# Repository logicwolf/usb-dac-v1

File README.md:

# usb-dac-v1

This is project for making the usb-dac with pcm2707 and es9023 - 2017.01.24

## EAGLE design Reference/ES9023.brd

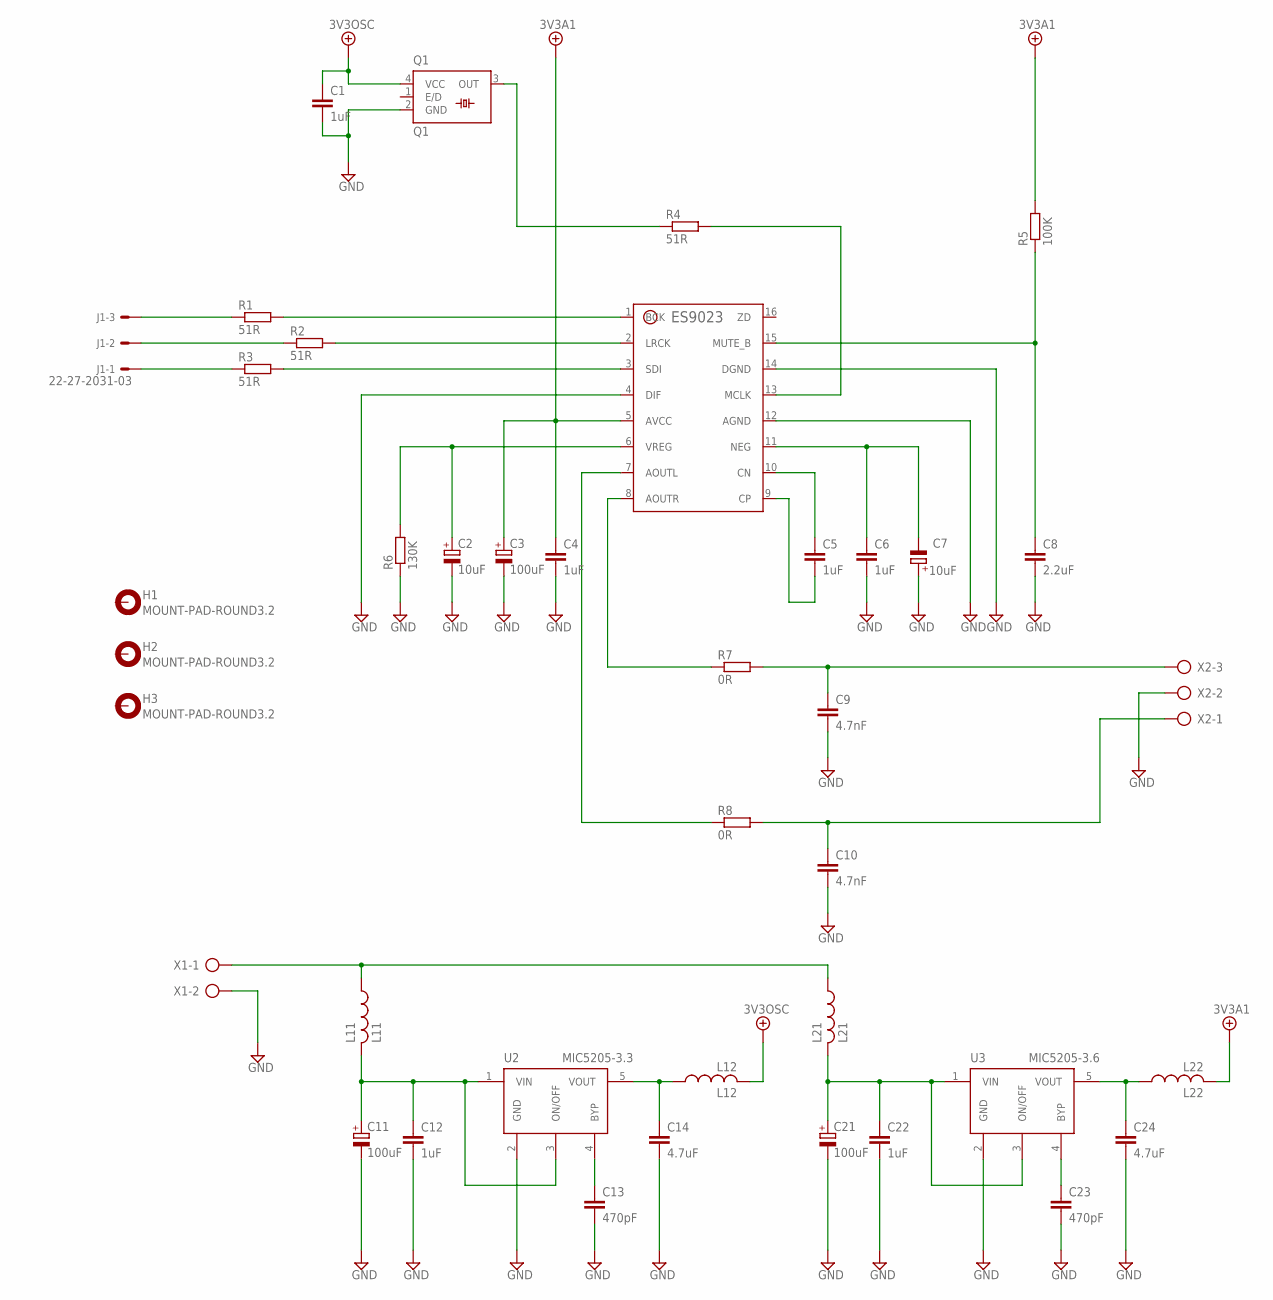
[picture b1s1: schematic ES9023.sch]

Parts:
C1, C4, C5, C6, C12, C22: 1uF; C1210
C2, C7: 10uF; E2,5-5
C3, C11, C21: 100uF; E2,5-5
C8: 2.2uF; C0805
C9, C10: 4.7nF; 5.08MM
C13, C23: 470pF; C0805
C14, C24: 4.7uF; C1210
H1, H2, H3: MOUNT-PAD-ROUND3.2; 3,2-PAD
J1: 22-27-2031-03; 6410-03
L11: L11; 1812
L12: L12; R1206
L21: L21; 1812
L22: L22; R1206
Q1: Q1; SM77H
R1, R2, R3, R4: 51R; R0805
R5: 100K; R0805
R6: 130K; R0805
R7, R8: 0R; R0805
U1: ES9023; SOP-16
U2: MIC5205-3.3; SOT23-5
U3: MIC5205-3.6; SOT23-5
X1: AK300/2
X2: AK300/3

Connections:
+3.3V: C1.1, L12.2, Q1.4 (VCC)
+5V/1: C3.+, C4.1, L22.2, R5.2, U1.5 (AVCC)
GND: C1.2, C2.-, C3.-, C4.2, C6.2, C7.+, C8.2, C9.2, C10.2, C11.-, C12.2, C13.2, C14.2, C21.-, C22.2, C23.2, C24.2, Q1.2 (GND), R6.1, U1.4 (DIF), U1.12 (AGND), U1.14 (DGND), U2.2 (GND), U3.2 (GND), X1.2, X2.2
unnamed: J1.3, R1.1
unnamed: J1.2, R2.1
unnamed: J1.1, R3.1
unnamed: R1.2, U1.1 (BCK)
unnamed: R2.2, U1.2 (LRCK)
unnamed: R3.2, U1.3 (SDI)
unnamed: L11.1, L21.1, X1.1
unnamed: C10.1, R8.2, X2.1
unnamed: C2.+, R6.2, U1.6 (VREG)
unnamed: R8.1, U1.7 (AOUTL)
unnamed: R7.1, U1.8 (AOUTR)
unnamed: C11.+, C12.1, L11.2, U2.1 (VIN), U2.3 (ON/OFF)
unnamed: C13.1, U2.4 (BYP)
unnamed: Q1.3 (OUT), R4.1
unnamed: R4.2, U1.13 (MCLK)
unnamed: C8.1, R5.1, U1.15 (MUTE_B)
unnamed: C14.1, L12.1, U2.5 (VOUT)
unnamed: C6.1, C7.-, U1.11 (NEG)
unnamed: C5.1, U1.10 (CN)
unnamed: C5.2, U1.9 (CP)
unnamed: C9.1, R7.2, X2.3
unnamed: C21.+, C22.1, L21.2, U3.1 (VIN), U3.3 (ON/OFF)
unnamed: C23.1, U3.4 (BYP)
unnamed: C24.1, L22.1, U3.5 (VOUT)

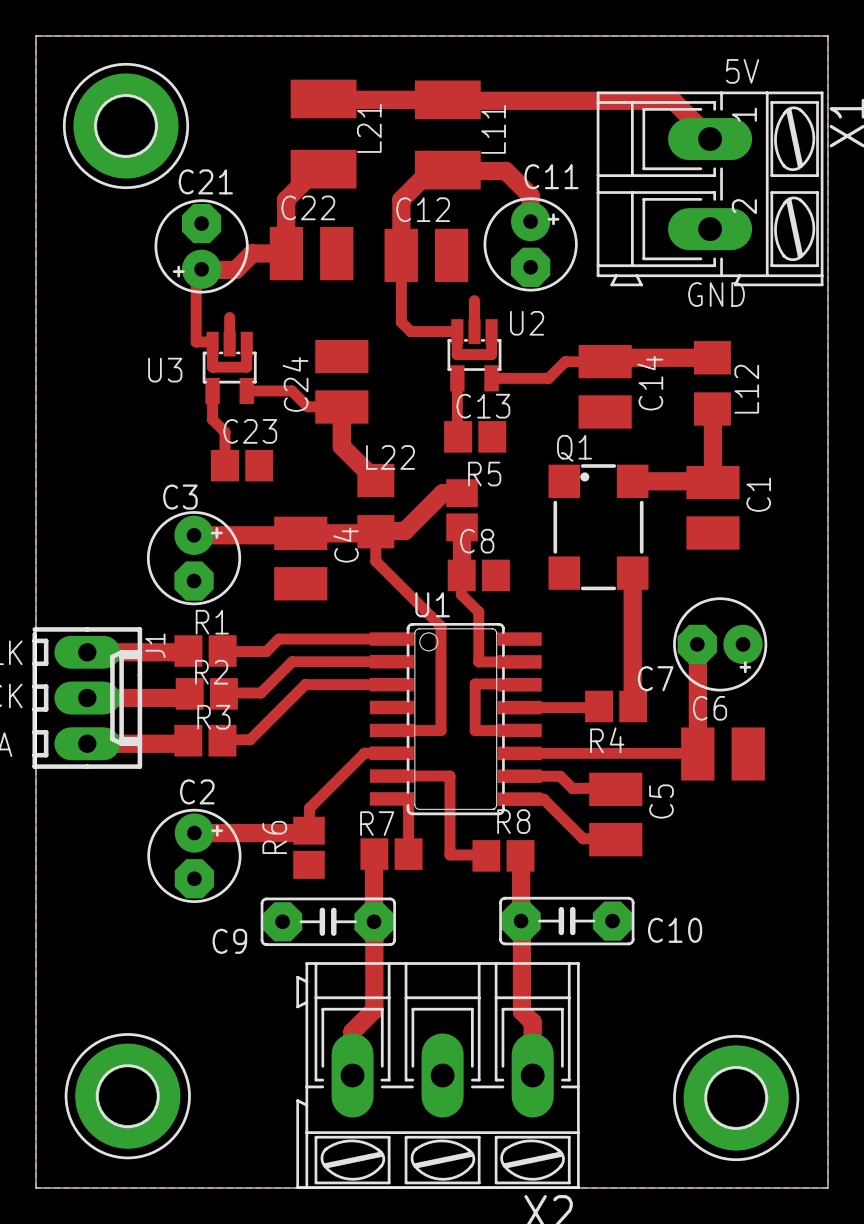
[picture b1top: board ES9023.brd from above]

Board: 2 copper layers, 44.0 x 64.0 mm, 40 parts (0 on the bottom side), 27 nets.

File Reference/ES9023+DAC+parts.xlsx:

S. No | Part Identifier | Quantitiy | Value | Manufacturer Part Number | Package
1 | Capacitors
2 | C1, C4, C12, C22 | 4 | 1uF | GRM32RR71H105KA01L | C1210
3 | C2, C7 | 2 | 10uF | RFS-35V100ME3#5 | E2,5-5
4 | C3, C11, C21 | 3 | 100uF | RNE1C101MDS1PX | E2,5-5
5 | C5, C6 | 2 | 1uF | ECP-U1C105MA5 | C1210
6 | C8 | 1 | 2.2uF | GRM21BR71A225KA01L | C0805
7 | C9, C10 | 2 | 4.7nF | BFC237051472 | 5.08mm LS
8 | C13, C23 | 2 | 470pF | GRM2165C1H471JA01D | C0805
9 | C14, C24 | 2 | 4.7uF | EMK316B7475KL-T | C1210
 | Resistors
10 | R1, R2, R3, R4 | 4 | 51R | RR1220Q-510-D | R0805
11 | R5 | 1 | 100K | RR1220P-104-D | R0805
12 | R6 | 1 | 130K | RR1220P-134-D | R0805
13 | R7, R8 | 2 | 0R | MCU08050Z0000ZP500 | R0805
 |  |  |  | TNPW080510R0BEEA
 | Inductors
14 | L11, L21 | 2 | RF Inductors 100uH | CM453232-101KL | 1812
15 | L12, L22 | 2 |  | BLM31PG601SN1L | R1206
 | Semiconductors
16 | U1 | 1 | ES9023 |  | SOP-16
17 | U2 | 1 | MIC5205-3.3 | MIC5205-3.3YM5 TR | SOT23-5
18 | U3 | 1 | MIC5205-3.6 | MIC5205-3.6YM5 TR | SOT23-5
 | Oscillator
19 | Q1 | 1 | 50MHz | ASV-50.000MHZ-E-J-T | SM77H

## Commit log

2017-01-16 modify README.md file to explain project
2017-01-16 again
2017-01-23 Modify Readme
2017-01-23 Added reference circuit from internet

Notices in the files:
parts and their libraries:
USB_ES9023 DAC: (c) 2004  Simon Cihelnik
